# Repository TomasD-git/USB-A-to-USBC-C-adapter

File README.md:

# USB-A-to-USBC-C-adapter
**Compact USB-A to USB-C adapter, supports USB 3.1 speeds, with stable power**

<details>
<summary>Features</summary>
  
-Small  
-Very fast  
-1 Layer PCBA  
  
</details>

<details>
  <summary>BOM</summary>

# BOM
 
| Name | Purpose | Quantity | Total Cost (USD) | Link | Distributor |
|------|---------|----------|-----------------|------|-------------|
| PCB | all components are on this | 1 | 15 | [jlcpcb](https://jlcpcb.com) | jlcpcb |
| ALL components | all components that are on pcb | 1 | 25 | [lcsc](https://lcsc.com) | lcsc |
| | | **Total cost** | **40** | | |

</details>

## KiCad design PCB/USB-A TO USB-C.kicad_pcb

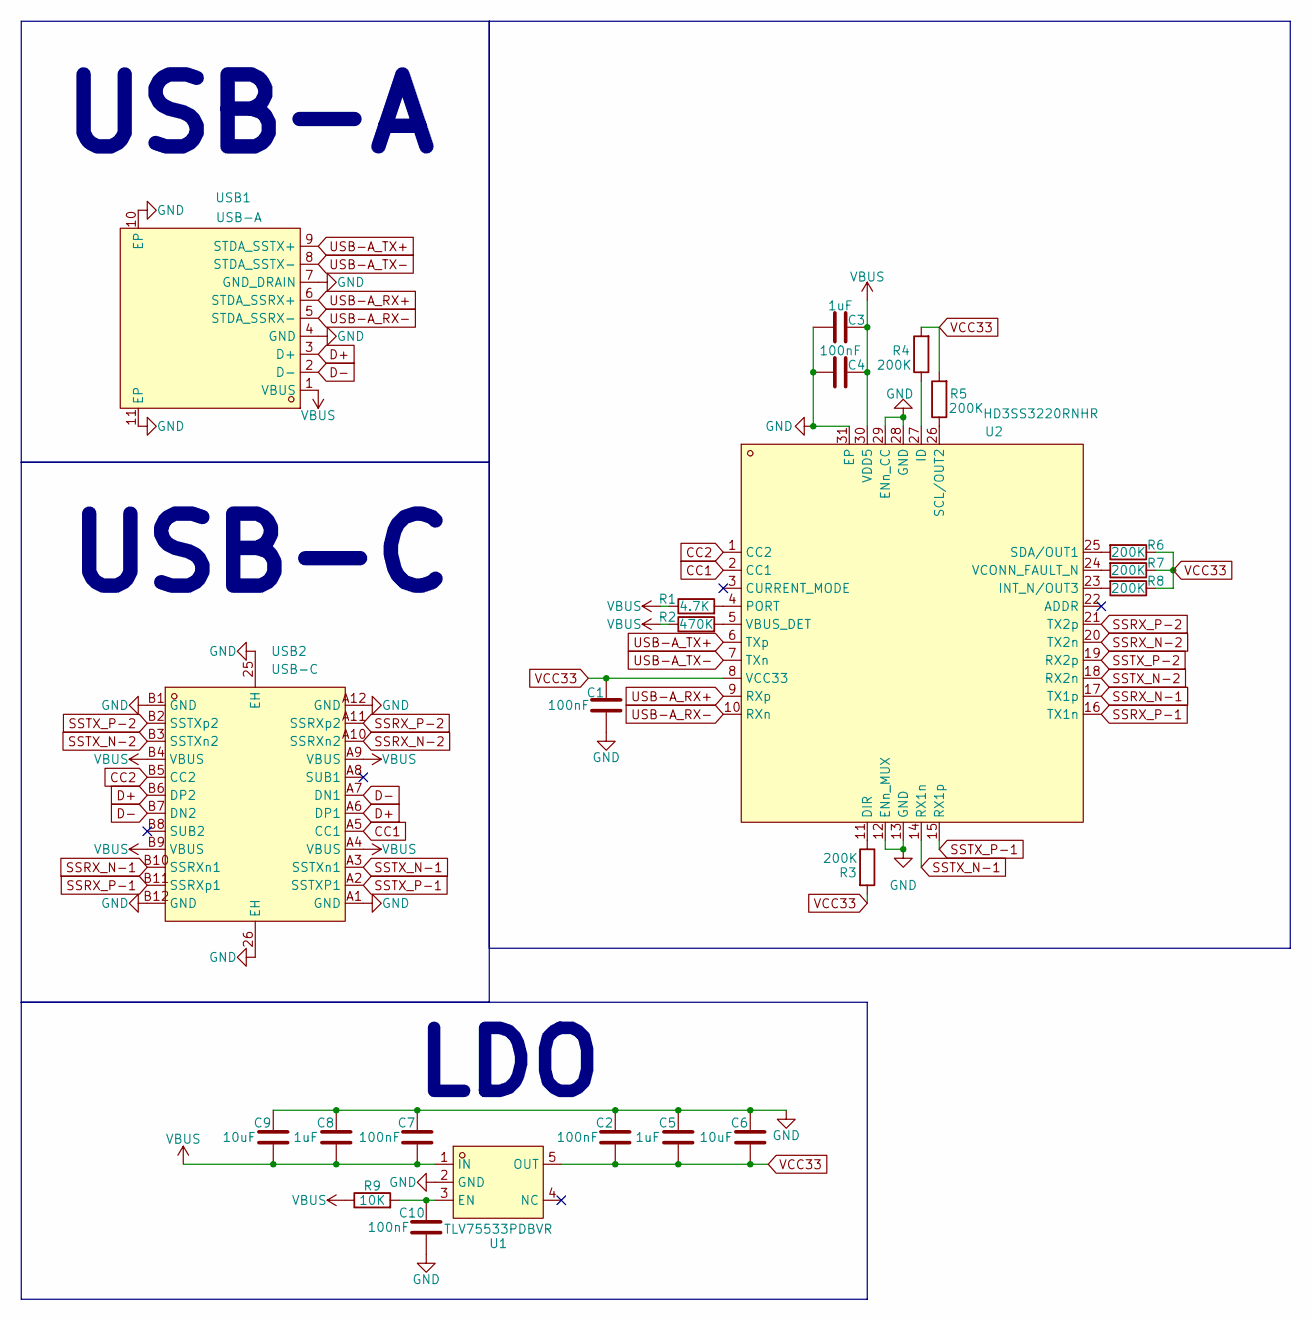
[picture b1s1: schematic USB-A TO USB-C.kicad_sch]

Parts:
C1, C2, C4, C7, C10: 100nF; C_0402_1005Metric_Pad0.74x0.62mm_HandSolder
C3, C5, C8: 1uF; C_0603_1608Metric
C6, C9: 10uF; C_0805_2012Metric
R1: 4.7K; R_0603_1608Metric
R2: 470K; R_0603_1608Metric
R3, R4, R5, R6, R7, R8: 200K; R_0603_1608Metric
R9: 10K; R_0603_1608Metric
U1: TLV75533PDBVR; SOT-23-5_L3.0-W1.7-P0.95-LS2.8-BR; MPN TLV75533PDBVR; LCSC Part C404027
U2: HD3SS3220RNHR; WQFN-30_L4.5-W2.5-P0.4-BL-EP; MPN HD3SS3220RNHR; LCSC Part C165155
USB1: USB-A; USB-A-SMD_U-A-39WD-W-1; MPN U-A-39WD-W-1; LCSC Part C3020886
USB2: USB-C; USB-C-SMD_USB-3.1-C-TYPE; MPN XDBM-0339-1530; LCSC Part C7527710

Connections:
CC1: U2.2 (CC1), USB2.A5 (CC1)
CC2: U2.1 (CC2), USB2.B5 (CC2)
D+: USB1.3 (D+), USB2.A6 (DP1), USB2.B6 (DP2)
D-: USB1.2 (D-), USB2.A7 (DN1), USB2.B7 (DN2)
GND: C1.1, C2.2, C3.1, C4.1, C5.2, C6.2, C7.2, C8.2, C9.2, C10.1, U1.2 (GND), U2.12 (ENn_MUX), U2.13 (GND), U2.28 (GND), U2.29 (ENn_CC), U2.31 (EP), USB1.4 (GND), USB1.7 (GND_DRAIN), USB1.10 (EP), USB1.11 (EP), USB2.25 (EH), USB2.26 (EH), USB2.A1 (GND), USB2.A12 (GND), USB2.B1 (GND), USB2.B12 (GND)
unnamed: C10.2, R9.2, U1.3 (EN)
unnamed: R3.1, U2.11 (DIR)
unnamed: R4.1, U2.27 (ID)
unnamed: R8.2, U2.23 (INT_N/OUT3)
unnamed: R1.2, U2.4 (PORT)
unnamed: R5.1, U2.26 (SCL/OUT2)
unnamed: R6.2, U2.25 (SDA/OUT1)
unnamed: R2.2, U2.5 (VBUS_DET)
unnamed: R7.2, U2.24 (VCONN_FAULT_N)
SSRX_N-1: U2.17 (TX1p), USB2.B10 (SSRXn1)
SSRX_N-2: U2.20 (TX2n), USB2.A10 (SSRXn2)
SSRX_P-1: U2.16 (TX1n), USB2.B11 (SSRXp1)
SSRX_P-2: U2.21 (TX2p), USB2.A11 (SSRXp2)
SSTX_N-1: U2.14 (RX1n), USB2.A3 (SSTXn1)
SSTX_N-2: U2.18 (RX2n), USB2.B3 (SSTXn2)
SSTX_P-1: U2.15 (RX1p), USB2.A2 (SSTXP1)
SSTX_P-2: U2.19 (RX2p), USB2.B2 (SSTXp2)
USB-A_RX+: U2.9 (RXp), USB1.6 (STDA_SSRX+)
USB-A_RX-: U2.10 (RXn), USB1.5 (STDA_SSRX-)
USB-A_TX+: U2.6 (TXp), USB1.9 (STDA_SSTX+)
USB-A_TX-: U2.7 (TXn), USB1.8 (STDA_SSTX-)
VBUS: C3.2, C4.2, C7.1, C8.1, C9.1, R1.1, R2.1, R9.1, U1.1 (IN), U2.30 (VDD5), USB1.1 (VBUS), USB2.A4 (VBUS), USB2.A9 (VBUS), USB2.B4 (VBUS), USB2.B9 (VBUS)
VCC33: C1.2, C2.1, C5.1, C6.1, R3.2, R4.2, R5.2, R6.1, R7.1, R8.1, U1.5 (OUT), U2.8 (VCC33)

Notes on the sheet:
USB-C
USB-A
LDO

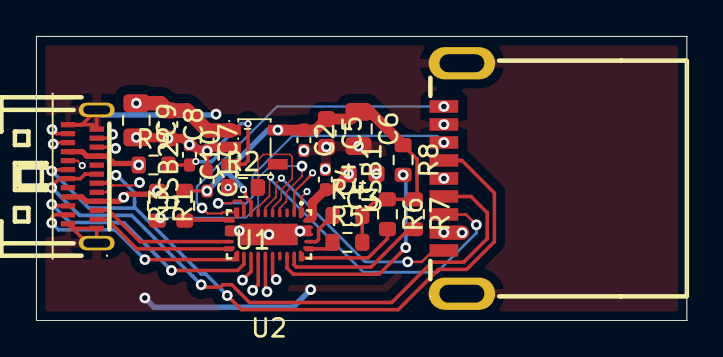
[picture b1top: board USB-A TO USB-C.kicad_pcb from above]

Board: 4 copper layers, 36.1 x 15.8 mm, 23 parts (0 on the bottom side), 28 nets.

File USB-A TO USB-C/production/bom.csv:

Designator,Footprint,Quantity,Value,LCSC Part #
"C1, C10, C2, C4, C7",0402,5,100nF,
"C3, C5, C8",0603,3,1uF,
"C6, C9",0805,2,10uF,
R1,0603,1,4.7K,
R2,0603,1,900K,
"R3, R4, R5, R6, R7, R8",0603,6,200K,
R9,0603,1,10K,
U1,SOT-23-5_L3.0-W1.7-P0.95-LS2.8-BR,1,TLV75533PDBVR,C404027
U2,WQFN-30_L4.5-W2.5-P0.4-BL-EP,1,HD3SS3220RNHR,C165155
USB1,USB-A-SMD_U-A-39WD-W-1,1,USB-A,C3020886
USB2,USB-C-SMD_USB-3.1-C-TYPE,1,USB-C,C7527710

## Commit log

2026-06-07 added files
2026-06-07 Enhance README with images and formatting
    Added images to enhance the README content.
2026-06-07 Add BOM section to README
    Added a Bill of Materials (BOM) section detailing components and costs.
2026-06-09 added new pcb files
2026-06-09 Update description for USB-A to USB-C adapter
2026-06-09 Update README with features and BOM sections
    Added features section to README with details.
2026-06-09 Fix formatting in README features section
